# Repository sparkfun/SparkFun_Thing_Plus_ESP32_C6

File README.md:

SparkFun Thing Plus - ESP32-C6
==============================

[*SparkFun Thing Plus - ESP32-C6 (DEV-22924)*](https://www.sparkfun.com/products/22924)

The SparkFun Thing Plus ESP32-C6 is a powerful wireless development board built around the ESP32-C6 WROOM-1-N16 wireless module from espressif<sup>&trade;</sup>. The ESP32-C6 is built around a single-core RISC-V processor with 16MB internal Flash memory. It supports WiFi 6, Bluetooth<sup>&reg;</sup> 5.3, Zigbee and Thread (802.12.4) wireless protocols and has a built-in PCB antenna. The ESP32-C6 has 23 multifunctional GPIO (*most* peripherals available on any GPIO), up to 7 12-bit ADC channels, up to 2 UARTs, USB Serial, one Low-Power UART, two I<sup>2</sup>C buses (one standard, one low-power), and one I<sup>2</sup>S bus.

This Thing Plus has a pair of 0.1"-spaced plated through hole (PTH) pins breaking out all of the ESP32's GPIO pins as well as connections for Reset, Boot, regulator enable, and the voltage rails (3.3V, USB, Battery), a USB-C connector, 2-pin JST connector for attaching a single-cell LiPo battery, MCP73831 battery charger, MAX17048 battery fuel gauge, 4-pin Qwiic connector, and &micro;SD card slot. The board has three LEDs for Power (Red), Battery Charge Indicator (Yellow), and STAT (RGB WS2812). The WS2812's data-in pin is tied to IO23 on the ESP32-C6.  

Repository Contents
-------------------

* **/Documents** - Datasheets, additional product information 
* **/Hardware** - Eagle design files (.brd, .sch)
* **/Production** - Production panel files (.brd)
* **/docs** - Documentation files for the Thing Plus ESP32-C6

Documentation
--------------

* **[Hookup Guide](https://docs.sparkfun.com/SparkFun_LTE_Stick_LARA_R6)** - Basic hookup guide for the SparkFun Thing Plus - ESP32-C6.

Product Versions
----------------
* [DEV-22924](https://www.sparkfun.com/products/22924) - Initial release

License Information
-------------------

This product is _**open source**_! 

Please review the LICENSE.md file for license information. 

If you have any questions or concerns on licensing, please contact technical support on our [SparkFun forums](https://forum.sparkfun.com/viewforum.php?f=152).

Distributed as-is; no warranty is given.

- Your friends at SparkFun.

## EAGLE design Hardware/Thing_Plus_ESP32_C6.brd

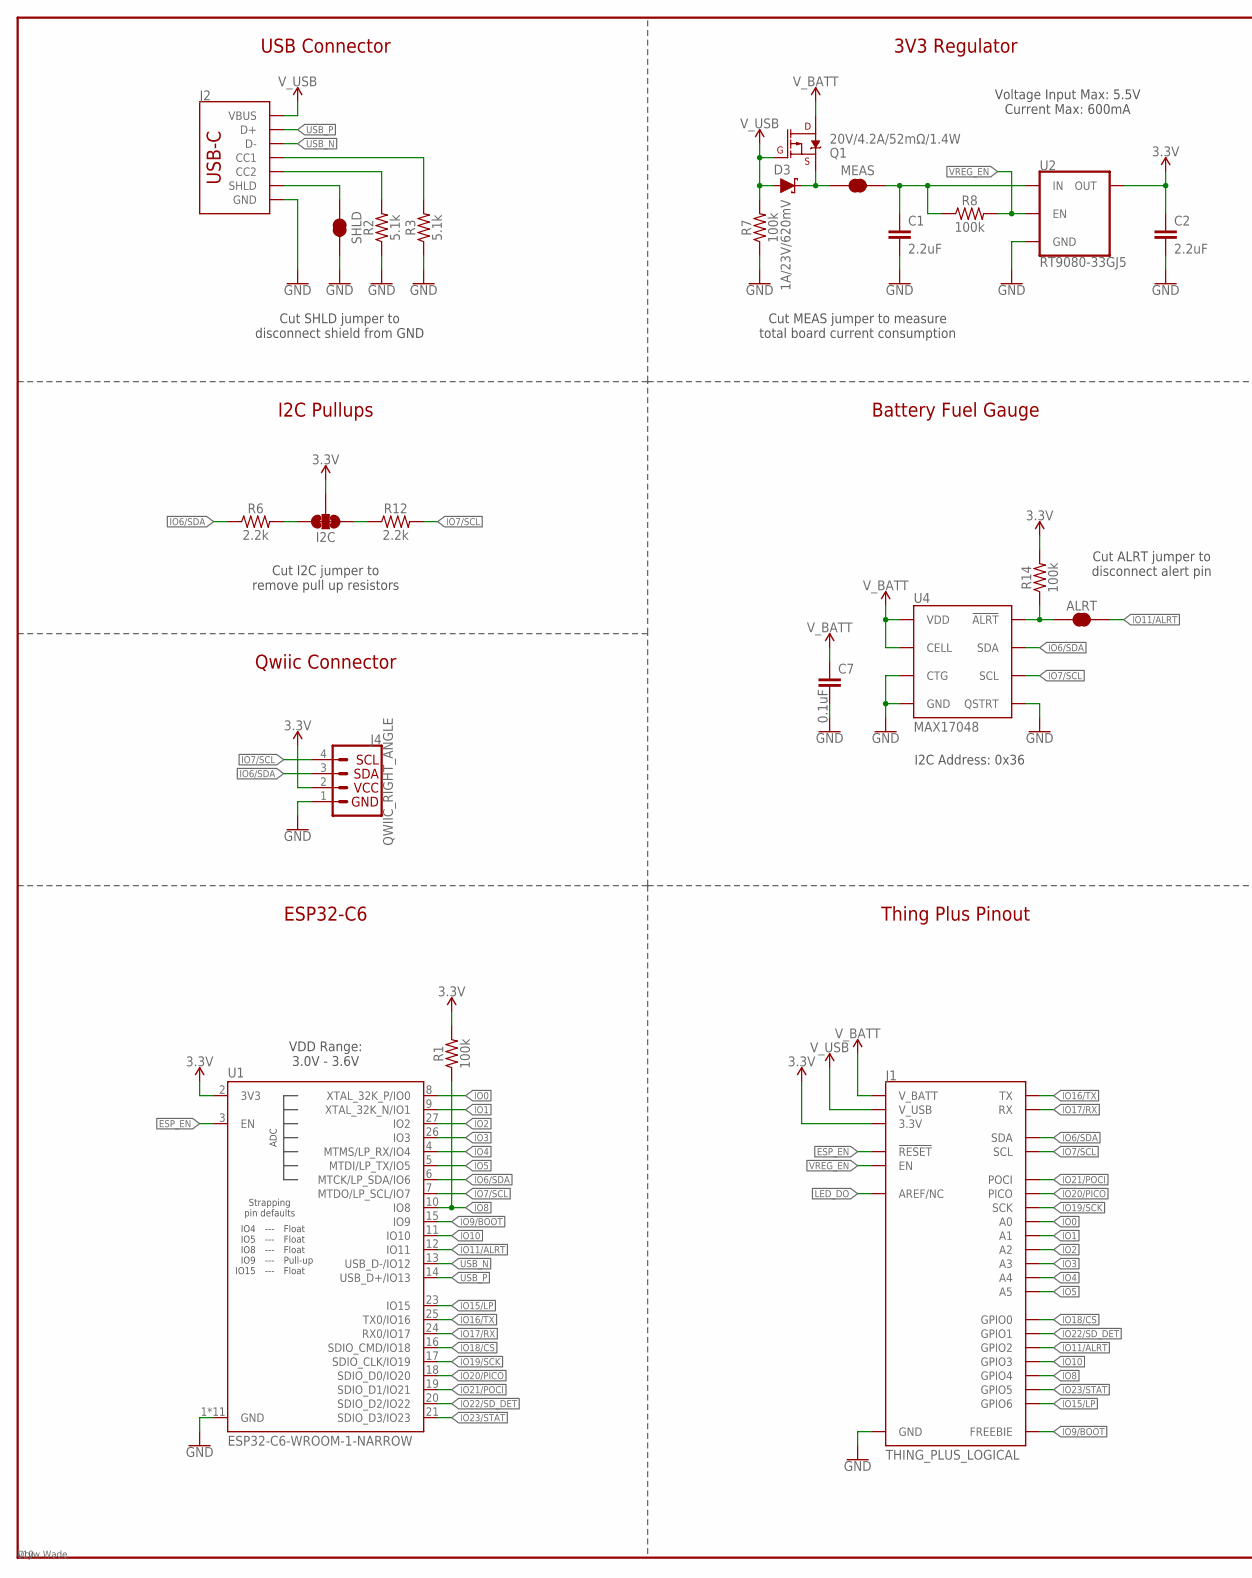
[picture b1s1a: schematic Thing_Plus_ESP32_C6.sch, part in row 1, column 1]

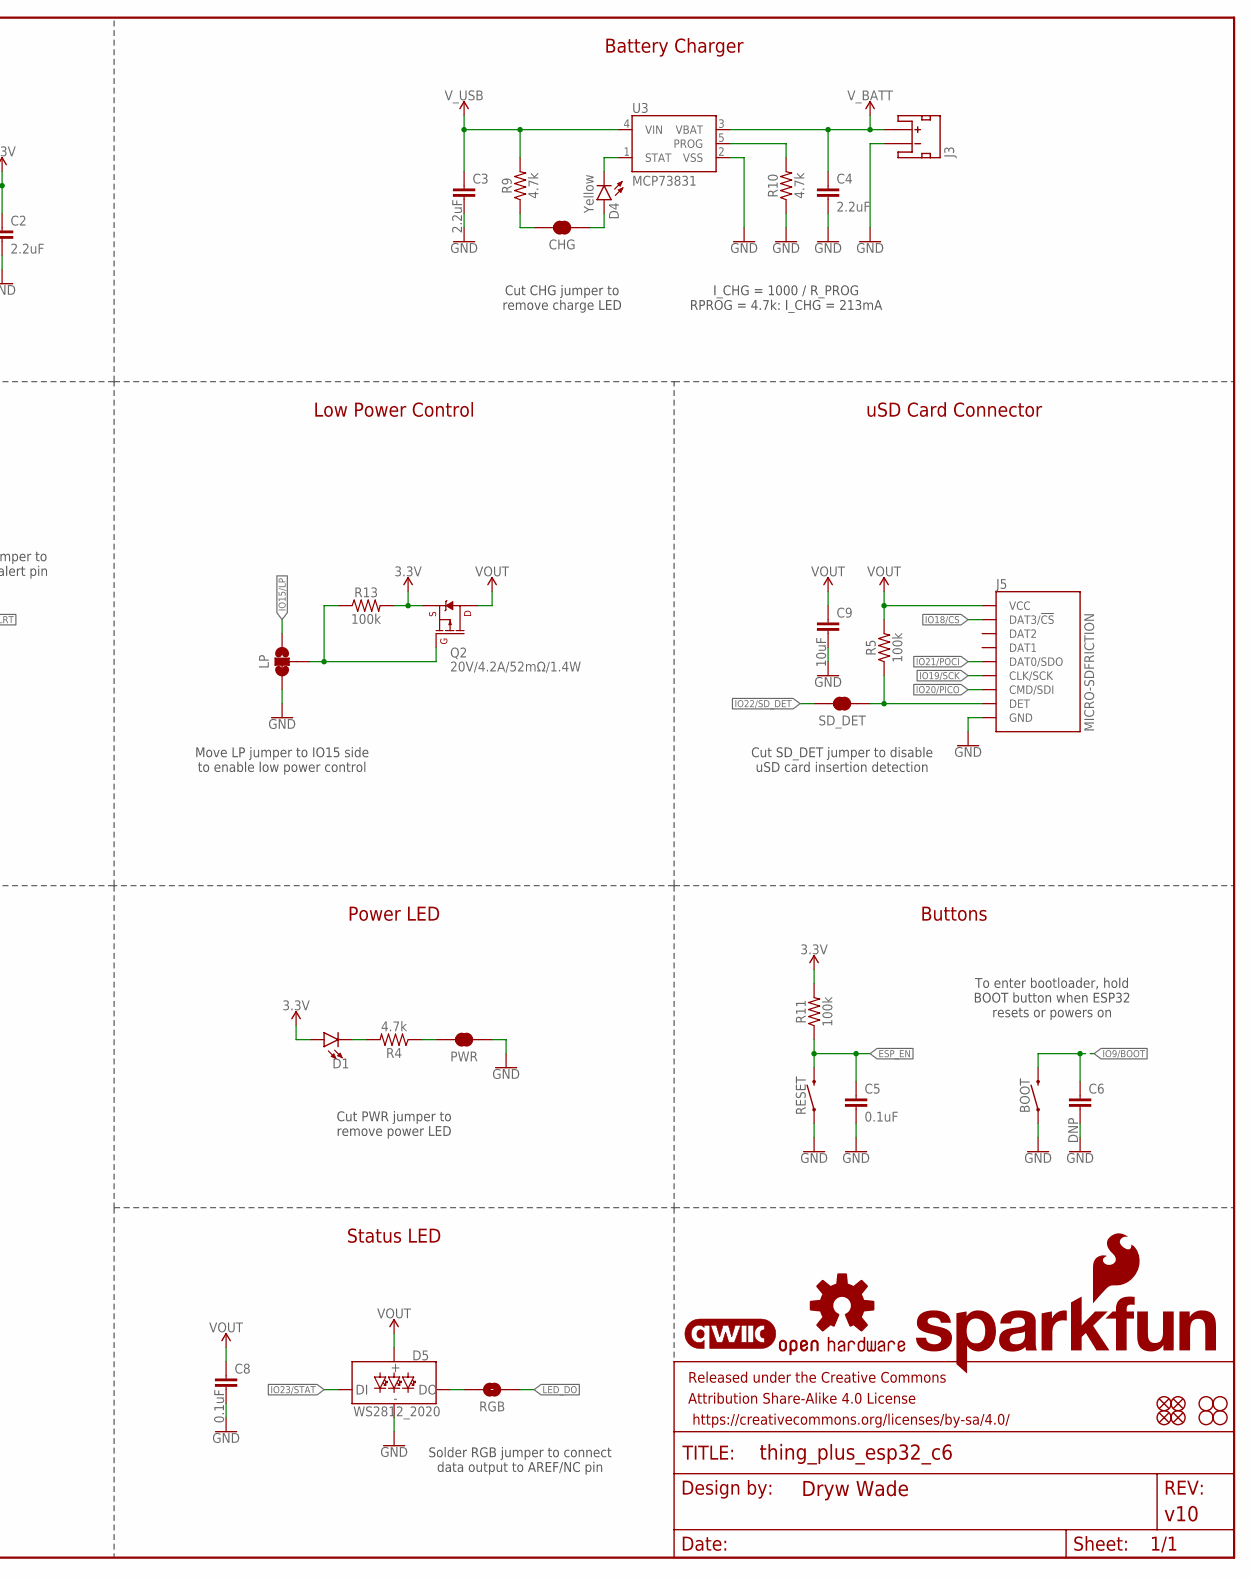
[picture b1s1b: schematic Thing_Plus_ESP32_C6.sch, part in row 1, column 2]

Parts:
ALRT: JUMPER-SMT_2_NC_TRACE_SILK; SMT-JUMPER_2_NC_TRACE_SILK
BOOT: MOMENTARY-SWITCH-SPST-SMD-4.6X2.8MM; TACTILE_SWITCH_SMD_4.6X2.8MM
C1, C2, C3, C4: 2.2uF; 0603
C5, C7, C8: 0.1uF; 0603
C6: DNP; 0603
C9: 10uF; 0603
CHG: JUMPER-SMT_2_NC_TRACE_SILK; SMT-JUMPER_2_NC_TRACE_SILK
D1: LED-RED_0603-KB; LED-0603
D3: 1A/23V/620mV; SOD-323
D4: Yellow; LED-0603
D5: WS2812_2020; WS2812-2020
FD1, FD2, FD3, FD4: FIDUCIALUFIDUCIAL; FIDUCIAL-MICRO
FRAME1: FRAME-LEDGER; CREATIVE_COMMONS
H1, H2, H3, H4: STAND-OFF
I2C: JUMPER-SMT_3_2-NC_TRACE_SILK; SMT-JUMPER_3_2-NC_TRACE_SILK
J1: THING_PLUS_LOGICAL; THING_PLUS
J2: USB_C_4-LAYER_PADS; USB-C-16P_4LAYER-PADS
J3: JST_2MM_MALE; JST-2-SMD
J4: QWIIC_RIGHT_ANGLE; JST04_1MM_RA
J5: MICRO-SDFRICTION; MICROSD_TINY
LOGO1: SFE_LOGO_NAME_FLAME.1_INCH; SFE_LOGO_NAME_FLAME_.1
LOGO2: QWIIC_LOGO_4MM; QWIIC_4MM
LOGO3: OSHW-LOGOM; OSHW-LOGO-M
LP: JUMPER-SMT_3_1-NC_TRACE_SILK; SMT-JUMPER_3_1-NC_TRACE_SILK
MEAS: JUMPER-COMBO_2_NC_TRACE; COMBO-JUMPER_2_NC_TRACE
PWR: JUMPER-SMT_2_NC_TRACE_SILK; SMT-JUMPER_2_NC_TRACE_SILK
Q1, Q2: 20V/4.2A/52mΩ/1.4W; SOT23-3
R1, R5, R7, R8, R11, R13, R14: 100k; 0603
R2, R3: 5.1k; 0603
R4, R9, R10: 4.7k; 0603
R6, R12: 2.2k; 0603
RESET: MOMENTARY-SWITCH-SPST-SMD-4.6X2.8MM; TACTILE_SWITCH_SMD_4.6X2.8MM
RGB: JUMPER-SMT_2_NO_SILK; SMT-JUMPER_2_NO_SILK
SD_DET: JUMPER-SMT_2_NC_TRACE_SILK; SMT-JUMPER_2_NC_TRACE_SILK
SHLD: JUMPER-SMT_2_NC_TRACE_SILK; SMT-JUMPER_2_NC_TRACE_SILK
U1: ESP32-C6-WROOM-1-NARROW
U2: RT9080-33GJ5; SOT23-5
U3: MCP73831; SOT23-5
U4: MAX17048; DFN-8

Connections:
3.3V: C2.1, D1.A, I2C.2, J1.27 (3.3V), J4.2, Q2.2 (S), R1.2, R11.2, R13.2, R14.2, U1.2 (3V3), U2.5 (OUT)
ESP_EN: C5.1, J1.28 (!RESET), R11.1, RESET.3 (2), RESET.4 (2), U1.3 (EN)
GND: BOOT.1, BOOT.2 (1), C1.2, C2.2, C3.2, C4.2, C5.2, C6.2, C7.2, C8.2, C9.2, D5.GND, J1.25 (GND), J2.GND, J2.GND2 (GND), J3.1 (-), J4.1, J5.6 (GND), J5.GND1 (GND), J5.GND2 (GND), J5.GND3 (GND), J5.GND4 (GND), J5.GND5 (GND), J5.GND6 (GND), LP.3, PWR.1, R2.1, R3.1, R7.1, R10.1, RESET.1, RESET.2 (1), SHLD.2, U1.1 (GND), U1.28 (GND), U1.29 (GND), U1.30 (GND), U1.31 (GND), U1.32 (GND), U1.33 (GND), U1.34 (GND), U1.35 (GND), U1.36 (GND), U1.37 (GND), U2.2 (GND), U3.2 (VSS), U4.1 (CTG), U4.4 (GND), U4.6 (QSTRT), U4.9 (GND)
IO0: J1.24 (A0), U1.8 (XTAL_32K_P/IO0)
IO1: J1.23 (A1), U1.9 (XTAL_32K_N/IO1)
IO2: J1.22 (A2), U1.27 (IO2)
IO3: J1.21 (A3), U1.26 (IO3)
IO4: J1.20 (A4), U1.4 (MTMS/LP_RX/IO4)
IO5: J1.19 (A5), U1.5 (MTDI/LP_TX/IO5)
IO6/SDA: J1.1 (SDA), J4.3, R6.1, U1.6 (MTCK/LP_SDA/IO6), U4.8 (SDA)
IO7/SCL: J1.2 (SCL), J4.4, R12.2, U1.7 (MTDO/LP_SCL/IO7), U4.7 (SCL)
IO8: J1.5 (GPIO4), R1.1, U1.10 (IO8)
IO9/BOOT: BOOT.3 (2), BOOT.4 (2), C6.1, J1.13 (FREEBIE), U1.15 (IO9)
IO10: J1.6 (GPIO3), U1.11 (IO10)
IO11/!ALRT!: ALRT.2, J1.7 (GPIO2), U1.12 (IO11)
IO15/LP: J1.3 (GPIO6), LP.1, U1.23 (IO15)
IO16/TX: J1.14 (TX), U1.25 (TX0/IO16)
IO17/RX: J1.15 (RX), U1.24 (RX0/IO17)
IO18/!CS!: J1.9 (GPIO0), J5.2 (DAT3/!CS!), U1.16 (SDIO_CMD/IO18)
IO19/SCK: J1.18 (SCK), J5.5 (CLK/SCK), U1.17 (SDIO_CLK/IO19)
IO20/PICO: J1.17 (PICO), J5.3 (CMD/SDI), U1.18 (SDIO_D0/IO20)
IO21/POCI: J1.16 (POCI), J5.7 (DAT0/SDO), U1.19 (SDIO_D1/IO21)
IO22/!SD_DET!: J1.8 (GPIO1), SD_DET.2, U1.20 (SDIO_D2/IO22)
IO23/STAT: D5.DI, J1.4 (GPIO5), U1.21 (SDIO_D3/IO23)
LED_DO: J1.26 (AREF/NC), RGB.1
unnamed: D1.C, R4.2
unnamed: PWR.2, R4.1
unnamed: J5.9 (DET), R5.1, SD_DET.1
unnamed: D3.C, MEAS.1, MEAS.3 (1), Q1.2 (S)
unnamed: I2C.3, R6.2
unnamed: I2C.1, R12.1
unnamed: J2.B5 (CC2), R2.2
unnamed: J2.A5 (CC1), R3.2
unnamed: C1.1, MEAS.2, MEAS.4 (2), R8.1, U2.1 (IN)
unnamed: D4.C, U3.1 (STAT)
unnamed: CHG.1, D4.A
unnamed: CHG.2, R9.1
unnamed: R10.2, U3.5 (PROG)
unnamed: D5.DO, RGB.2
unnamed: LP.2, Q2.1 (G), R13.1
unnamed: ALRT.1, R14.1, U4.5 (!ALRT)
SHLD: J2.SHLD1 (SHLD), J2.SHLD2 (SHLD), J2.SHLD3 (SHLD), J2.SHLD4 (SHLD), SHLD.1
USB_N: J2.A7 (D-), J2.B7 (D-), U1.13 (USB_D-/IO12)
USB_P: J2.A6 (D+), J2.B6 (D+), U1.14 (USB_D+/IO13)
VOUT: C8.1, C9.1, D5.VCC, J5.4 (VCC), Q2.3 (D), R5.2
VREG_EN: J1.11 (EN), R8.2, U2.3 (EN)
V_BATT: C4.1, C7.1, J1.12 (V_BATT), J3.2 (+), Q1.3 (D), U3.3 (VBAT), U4.2 (CELL), U4.3 (VDD)
V_USB: C3.1, D3.A, J1.10 (V_USB), J2.VBUS1 (VBUS), J2.VBUS2 (VBUS), Q1.1 (G), R7.2, R9.2, U3.4 (VIN)

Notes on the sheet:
ESP32-C6
VDD Range: 3.0V - 3.6V
Buttons
3V3 Regulator
USB Connector
Battery Charger
Cut CHG jumper to remove charge LED
I_CHG = 1000 / R_PROG RPROG = 4.7k: I_CHG = 213mA
Power LED
Cut PWR jumper to remove power LED
Thing Plus Pinout
I2C Pullups
Cut I2C jumper to remove pull up resistors
I2C Address: 0x36
Qwiic Connector
Battery Fuel Gauge
uSD Card Connector
Cut SHLD jumper to disconnect shield from GND
Cut MEAS jumper to measure total board current consumption
Voltage Input Max: 5.5V Current Max: 600mA
Cut SD_DET jumper to disable uSD card insertion detection
Solder RGB jumper to connect data output to AREF/NC pin
Move LP jumper to IO15 side to enable low power control
To enter bootloader, hold BOOT button when ESP32 resets or powers on
Cut ALRT jumper to disconnect alert pin
Low Power Control
Status LED

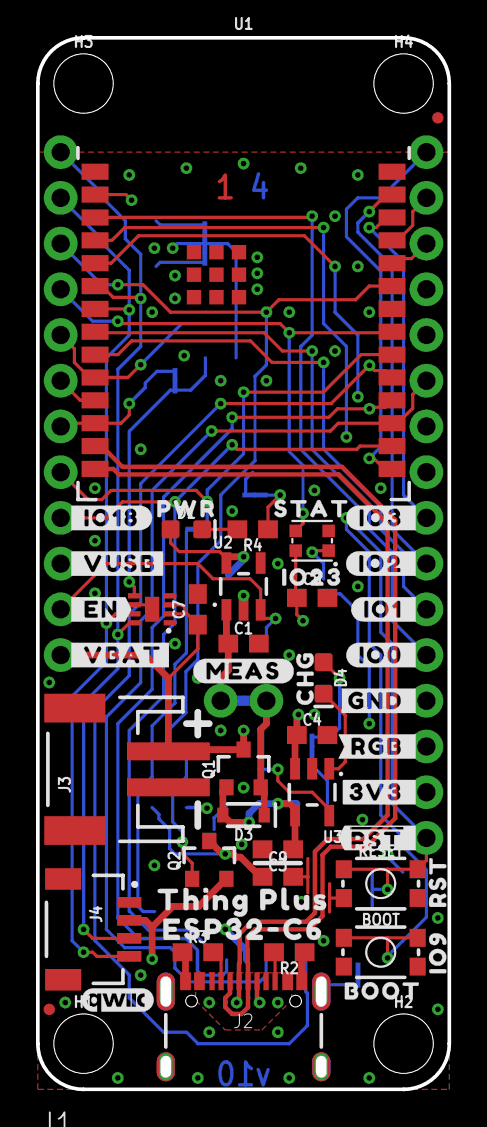
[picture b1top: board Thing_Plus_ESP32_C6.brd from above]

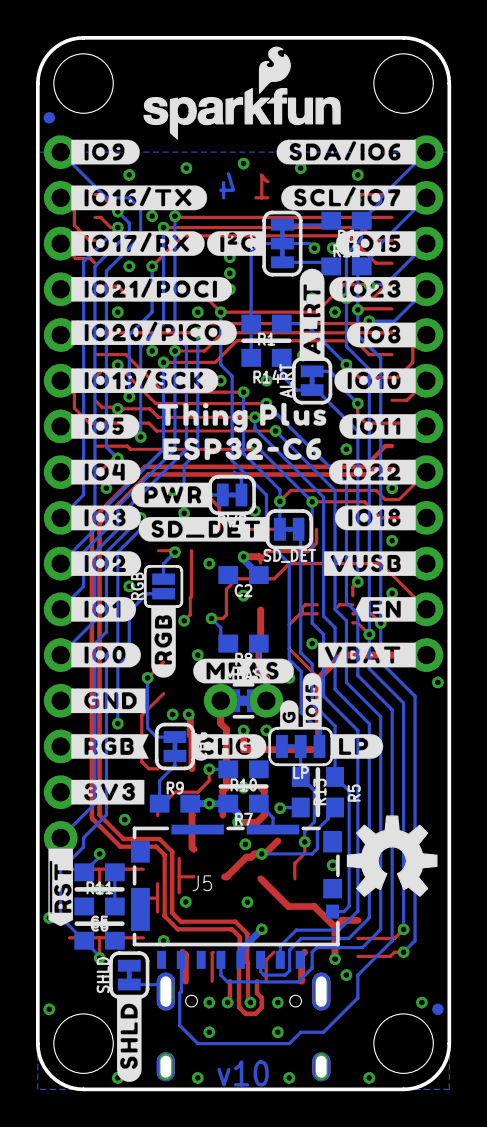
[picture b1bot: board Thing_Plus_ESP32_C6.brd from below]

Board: 4 copper layers, 22.9 x 58.4 mm, 125 parts (69 on the bottom side), 48 nets.

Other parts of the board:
U$1: #SHLD#0
U$2: #I�C#0
U$3: #_IO18#0
U$4: #_VUSB#0
U$5: #_VBAT#0
U$6: #_EN#0
U$7: #IO3_#0
U$8: #IO2_#0
U$9: #IO1_#0
U$10: #IO0_#0
U$11: #GND_#0
U$12: #3V3_#0
U$13, U$37: ##RST#_#0
U$14: #SDA#IO6_#0
U$15: #SCL#IO7_#0
U$16: #_IO21#POCI#0
U$17: #LP#0
U$18: #IO8_#0
U$19: #IO10_#0
U$20: #IO11_#0
U$21: #_IO19#SCK#0
U$22: #IO18_#0
U$23: #_IO9#0
U$24: #_IO16#TX#0
U$25: #_IO17#RX#0
U$26: #_IO20#PICO#0
U$27: #IO15#0
U$28: #ALRT#0
U$29: #_IO5#0
U$30: #_IO4#0
U$31: #_IO3#0
U$32: #_IO2#0
U$33: #_IO1#0
U$34: #_IO0#0
U$35: #_GND#0
U$36: #_3V3#0
U$38: #VUSB_#0
U$39: #VBAT_#0
U$40: #EN_#0
U$41: #SD_DET#0
U$42: BOOT0
U$43: RST0
U$44: IO90
U$45, U$47: THING_PLUS0
U$46, U$48: ESP32#C60
U$49, U$50: #MEAS#0
U$51: #CHG#0
U$52: #PWR#0
U$53: PWR0
U$54: CHG0
U$55: STAT0
U$56: #RGB#0
U$57: ORDERING_INSTRUCTIONS
U$58: #RGB_#0
U$59: #_RGB#0
U$62: IO230
U$63: #G#0
U$64: #IO23_#0
U$65: #IO15_#0
U$66: #IO22_#0

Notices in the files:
parts and their libraries:
SparkFun-Aesthetics: Licensing: Creative Commons ShareAlike 4.0 International - https://creativecommons.org/licenses/by-sa/4.0
SparkFun-Aesthetics: Released under the Creative Commons Attribution Share-Alike 4.0 License
SparkFun-Aesthetics: https://creativecommons.org/licenses/by-sa/4.0
